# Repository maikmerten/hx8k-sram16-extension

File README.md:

# hx8k-sram16-extension
A PCB with 4 Mbit of SRAM,  SPI-Flash, two LEDs, a button, SPI-connectors, and a single-row pmod-compatible connector for the Lattice HX8K Breakout Board. Connects to the headers **J3** and **J4** on the Lattice HX8K Breakout Board.

## WARNING: unstable

The board in its current state is difficult to operate in a stable manner. While signals to the SRAM-chip appear to be of decent quality, I've yet to achieve stable operation over extended periods of operation. This might be a matter of my SRAM-controller design within the FPGA, or an issue with the board design available here. Please be aware of this before considering deploying this design in your projects.

## BOM

| Component | Description | Qty. |
|-----------|-------------|------|
| U1 | 4 MBit SRAM chip, 256Kx16, e.g. AS7C34098A, 10ns or faster recommended, TSOP-II 44 package | 1 |
| U2 | SPI-Flash, e.g. W25Q32JV, 8-Pin SOIC package| 1 |
| C1, C2, C3 | 100nF ceramic capacitor, 0805 package | 3 |
| D1, D2 | SMD LEDs, red, 0805 package | 2 |
| R1, R2, R3, R4, R5, R6, R7, R8 | resistors, 1K, 0805 package | 8 |
| R9 | optional pull-up for SW1, anything between 10K and 50K should be fine, 0805 package | 1 |
| R10, R11 | resistors for the LEDs, 510 Ohm, 0805 package (**important:** populate before J3 and J4, as R10 and R11 will become inaccessible) | 2 |
| SW1 | 6x6 mm push button, THT | 1 |
| J1, J2 | 1x6 female header, 2.54 mm pin spacing | 2 |
| J3, J4 | 2x20 male pin headers, 2.54 mm pin spacing (**important:** solder on top side, so pins head downwards towards FPGA board)| 2 |
| J5 | 1x6 female right-angled header, 2.54 mm pin spacing | 1 |

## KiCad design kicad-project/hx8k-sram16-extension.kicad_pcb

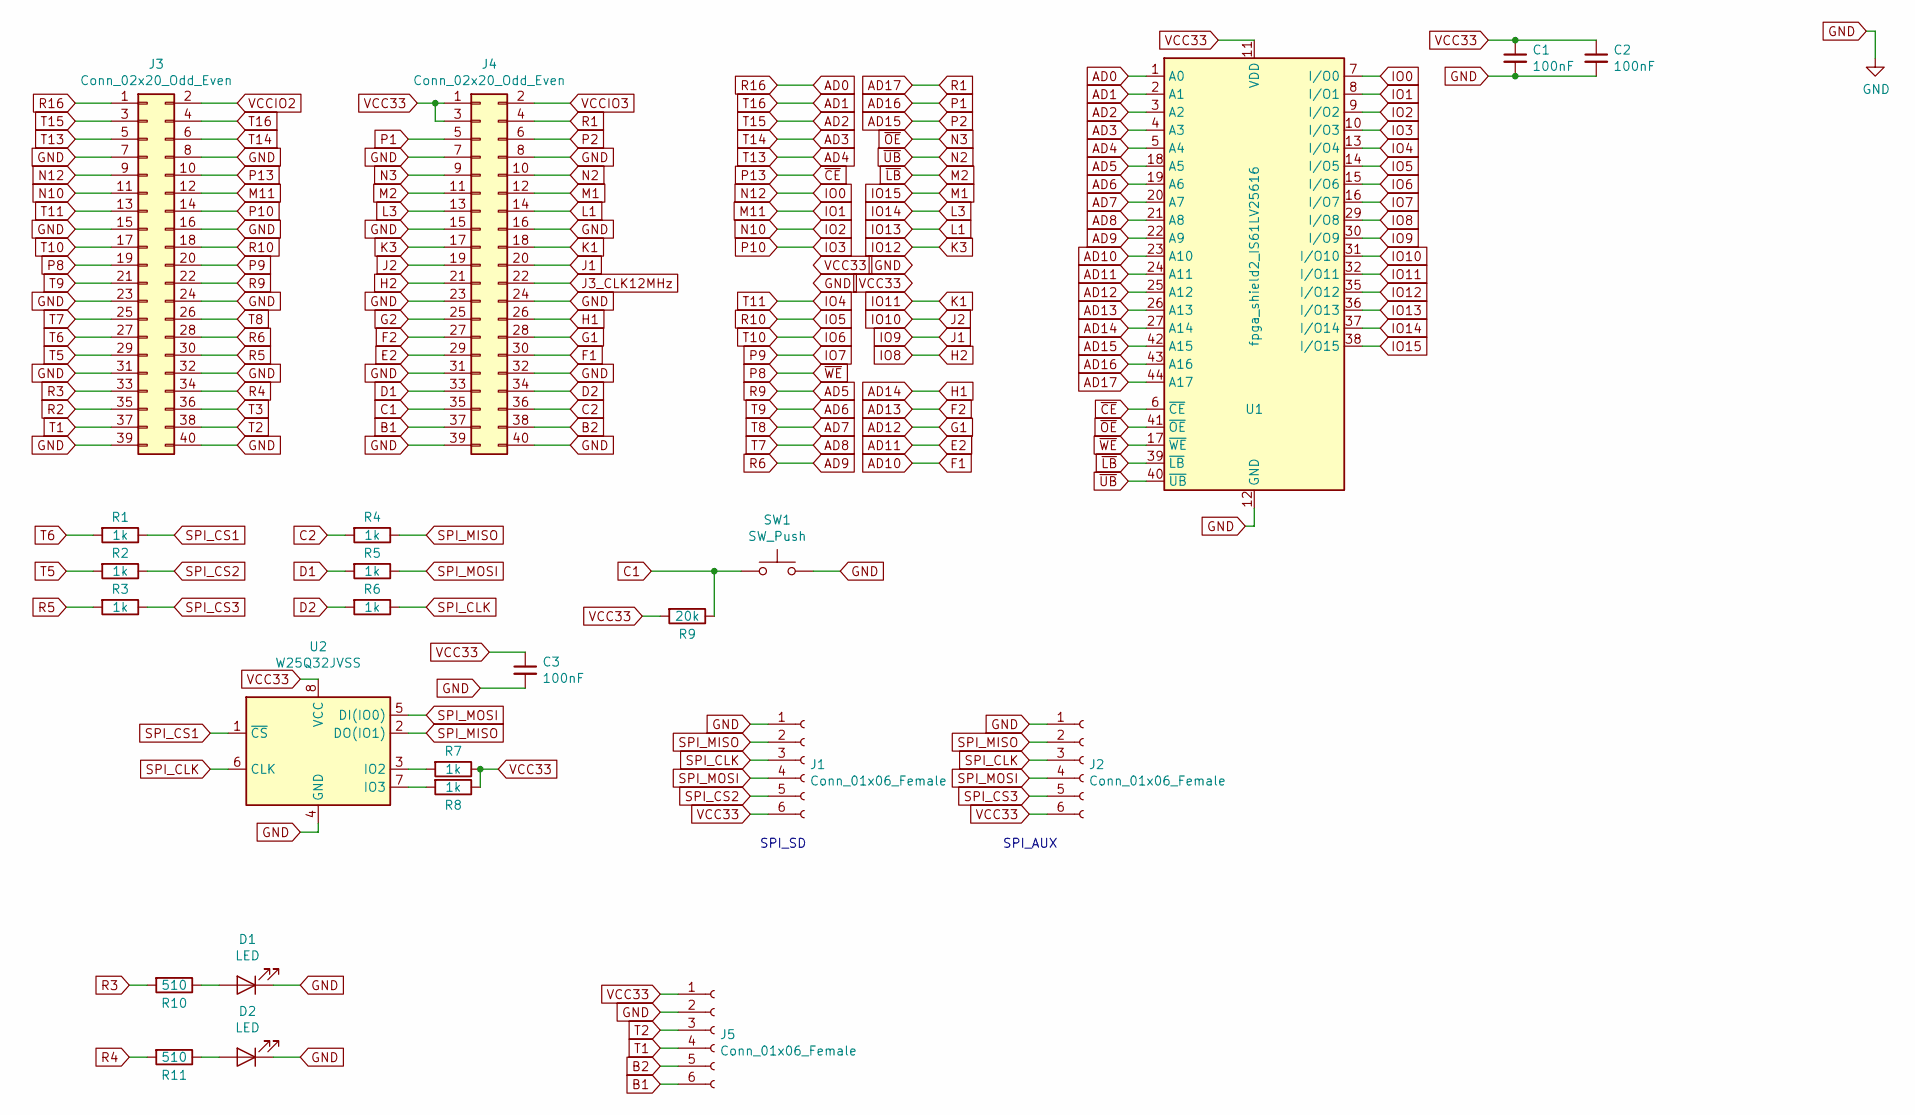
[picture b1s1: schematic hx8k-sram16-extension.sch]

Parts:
C1, C2, C3: 100nF; C_0805_2012Metric_Pad1.15x1.40mm_HandSolder
D1, D2: LED; LED_0805_2012Metric
J1, J2: Conn_01x06_Female; PinSocket_1x06_P2.54mm_Vertical
J3, J4: Conn_02x20_Odd_Even; PinHeader_2x20_P2.54mm_Vertical
J5: Conn_01x06_Female; PinSocket_1x06_P2.54mm_Horizontal
R1, R2, R3, R4, R5, R6, R7, R8: 1k; C_0805_2012Metric_Pad1.15x1.40mm_HandSolder
R9: 20k; C_0805_2012Metric_Pad1.15x1.40mm_HandSolder
R10, R11: 510; C_0805_2012Metric_Pad1.15x1.40mm_HandSolder
SW1: SW_Push; SW_PUSH_6mm
U1: fpga_shield2_IS61LV25616; TSOP-II-44_10.16x18.41mm_P0.8mm
U2: W25Q32JVSS; SOIJ-8_5.3x5.3mm_P1.27mm

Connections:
AD0: J3.1, U1.1 (A0)
AD1: J3.4, U1.2 (A1)
AD2: J3.3, U1.3 (A2)
AD3: J3.6, U1.4 (A3)
AD4: J3.5, U1.5 (A4)
AD5: J3.22, U1.18 (A5)
AD6: J3.21, U1.19 (A6)
AD7: J3.26, U1.20 (A7)
AD8: J3.25, U1.21 (A8)
AD9: J3.28, U1.22 (A9)
AD10: J4.30, U1.23 (A10)
AD11: J4.29, U1.24 (A11)
AD12: J4.28, U1.25 (A12)
AD13: J4.27, U1.26 (A13)
AD14: J4.26, U1.27 (A14)
AD15: J4.6, U1.42 (A15)
AD16: J4.5, U1.43 (A16)
AD17: J4.4, U1.44 (A17)
B1: J4.37, J5.6
B2: J4.38, J5.5
C1: J4.35, R9.1, SW1.1
C2: J4.36, R4.2
D1: J4.33, R5.2
D2: J4.34, R6.2
G2: J4.25
GND: C1.2, C2.2, C3.2, D1.1 (K), D2.1 (K), J1.1, J2.1, J3.7, J3.8, J3.15, J3.16, J3.23, J3.24, J3.31, J3.32, J3.39, J3.40, J4.7, J4.8, J4.15, J4.16, J4.23, J4.24, J4.31, J4.32, J4.39, J4.40, J5.2, SW1.2, U1.12 (GND), U1.34 (GND), U2.4 (GND)
H2: J4.21, U1.29 (I/O8)
IO0: J3.9, U1.7 (I/O0)
IO1: J3.12, U1.8 (I/O1)
IO2: J3.11, U1.9 (I/O2)
IO3: J3.14, U1.10 (I/O3)
IO4: J3.13, U1.13 (I/O4)
IO5: J3.18, U1.14 (I/O5)
IO6: J3.17, U1.15 (I/O6)
IO7: J3.20, U1.16 (I/O7)
IO9: J4.20, U1.30 (I/O9)
IO10: J4.19, U1.31 (I/O10)
IO11: J4.18, U1.32 (I/O11)
IO12: J4.17, U1.35 (I/O12)
IO13: J4.14, U1.36 (I/O13)
IO14: J4.13, U1.37 (I/O14)
IO15: J4.12, U1.38 (I/O15)
J3_CLK12MHz: J4.22
M2: J4.11, U1.39 (~LB)
N2: J4.10, U1.40 (~UB)
N3: J4.9, U1.41 (~OE)
unnamed: D1.2 (A), R10.1
unnamed: D2.2 (A), R11.1
unnamed: R7.2, U2.3 (IO2)
unnamed: R8.2, U2.7 (IO3)
P8: J3.19, U1.17 (~WE)
P13: J3.10, U1.6 (~CE)
R2: J3.35
R3: J3.33, R10.2
R4: J3.34, R11.2
R5: J3.30, R3.2
SPI_CLK: J1.3, J2.3, R6.1, U2.6 (CLK)
SPI_CS1: R1.1, U2.1 (~CS)
SPI_CS2: J1.5, R2.1
SPI_CS3: J2.5, R3.1
SPI_MISO: J1.2, J2.2, R4.1, U2.2 (DO(IO1))
SPI_MOSI: J1.4, J2.4, R5.1, U2.5 (DI(IO0))
T1: J3.37, J5.4
T2: J3.38, J5.3
T3: J3.36
T5: J3.29, R2.2
T6: J3.27, R1.2
VCC33: C1.1, C2.1, C3.1, J1.6, J2.6, J4.1, J4.3, J5.1, R7.1, R8.1, R9.2, U1.11 (VDD), U1.33 (VDD), U2.8 (VCC)
VCCIO2: J3.2
VCCIO3: J4.2

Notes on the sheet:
SPI_SD
SPI_AUX

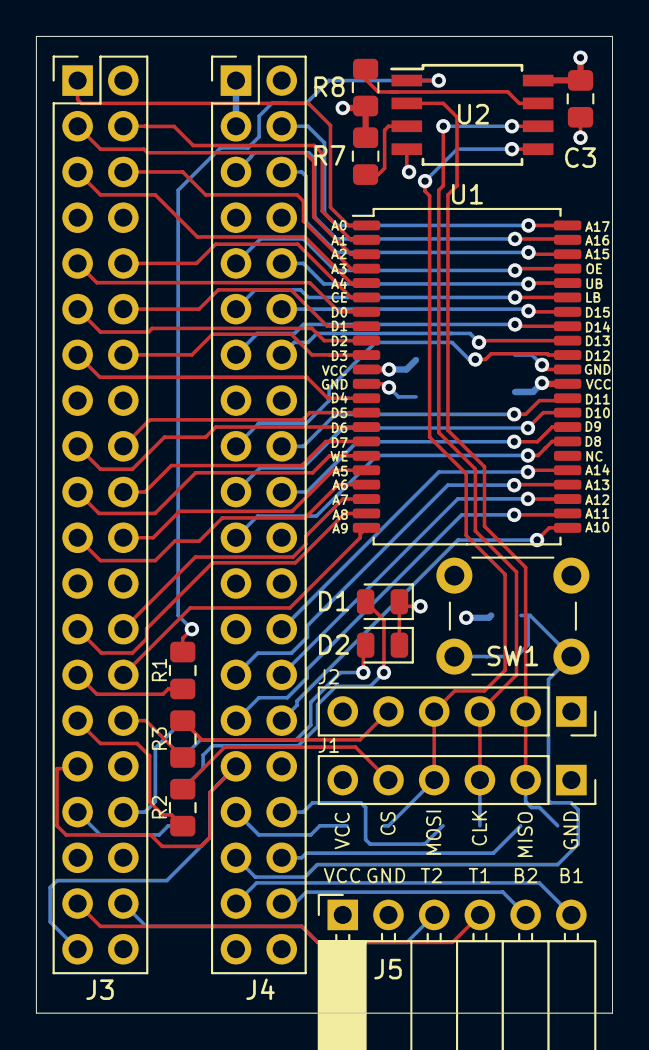
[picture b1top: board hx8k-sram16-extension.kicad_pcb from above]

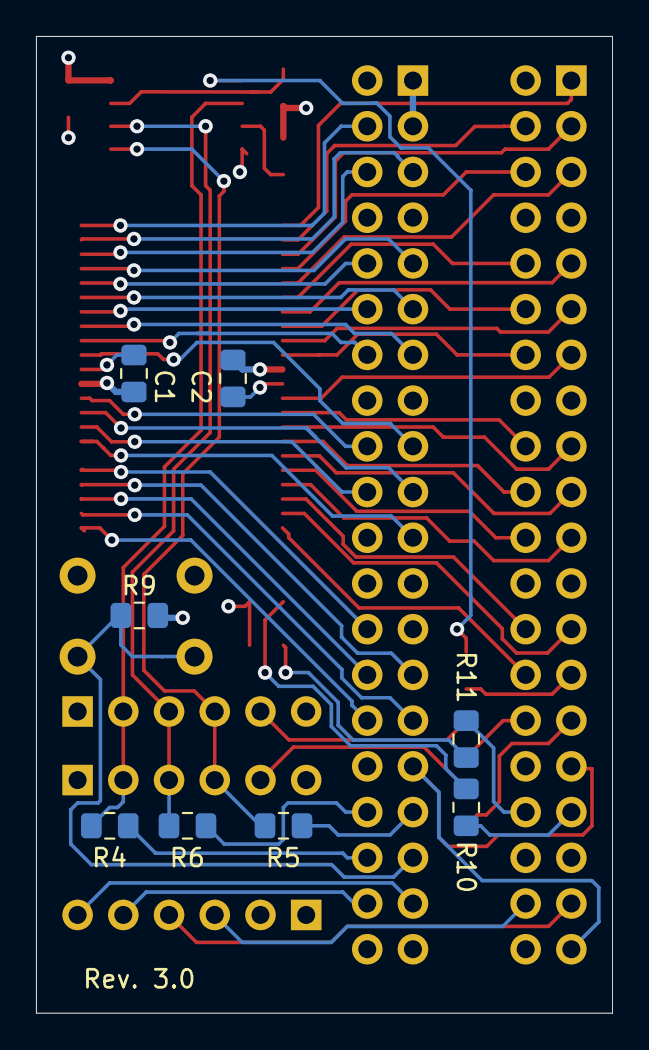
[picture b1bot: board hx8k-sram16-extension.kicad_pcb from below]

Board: 4 copper layers, 32.0 x 54.3 mm, 24 parts (8 on the bottom side), 64 nets.

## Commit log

2020-02-15 commit project files
2020-02-15 add gerber files
2020-02-15 add a picture of the PCB
2020-02-15 add README
2020-02-15 minor README update
2020-03-29 README: typo fix
2021-03-10 switch to four layers
2022-12-09 update README.md regarding board stability
